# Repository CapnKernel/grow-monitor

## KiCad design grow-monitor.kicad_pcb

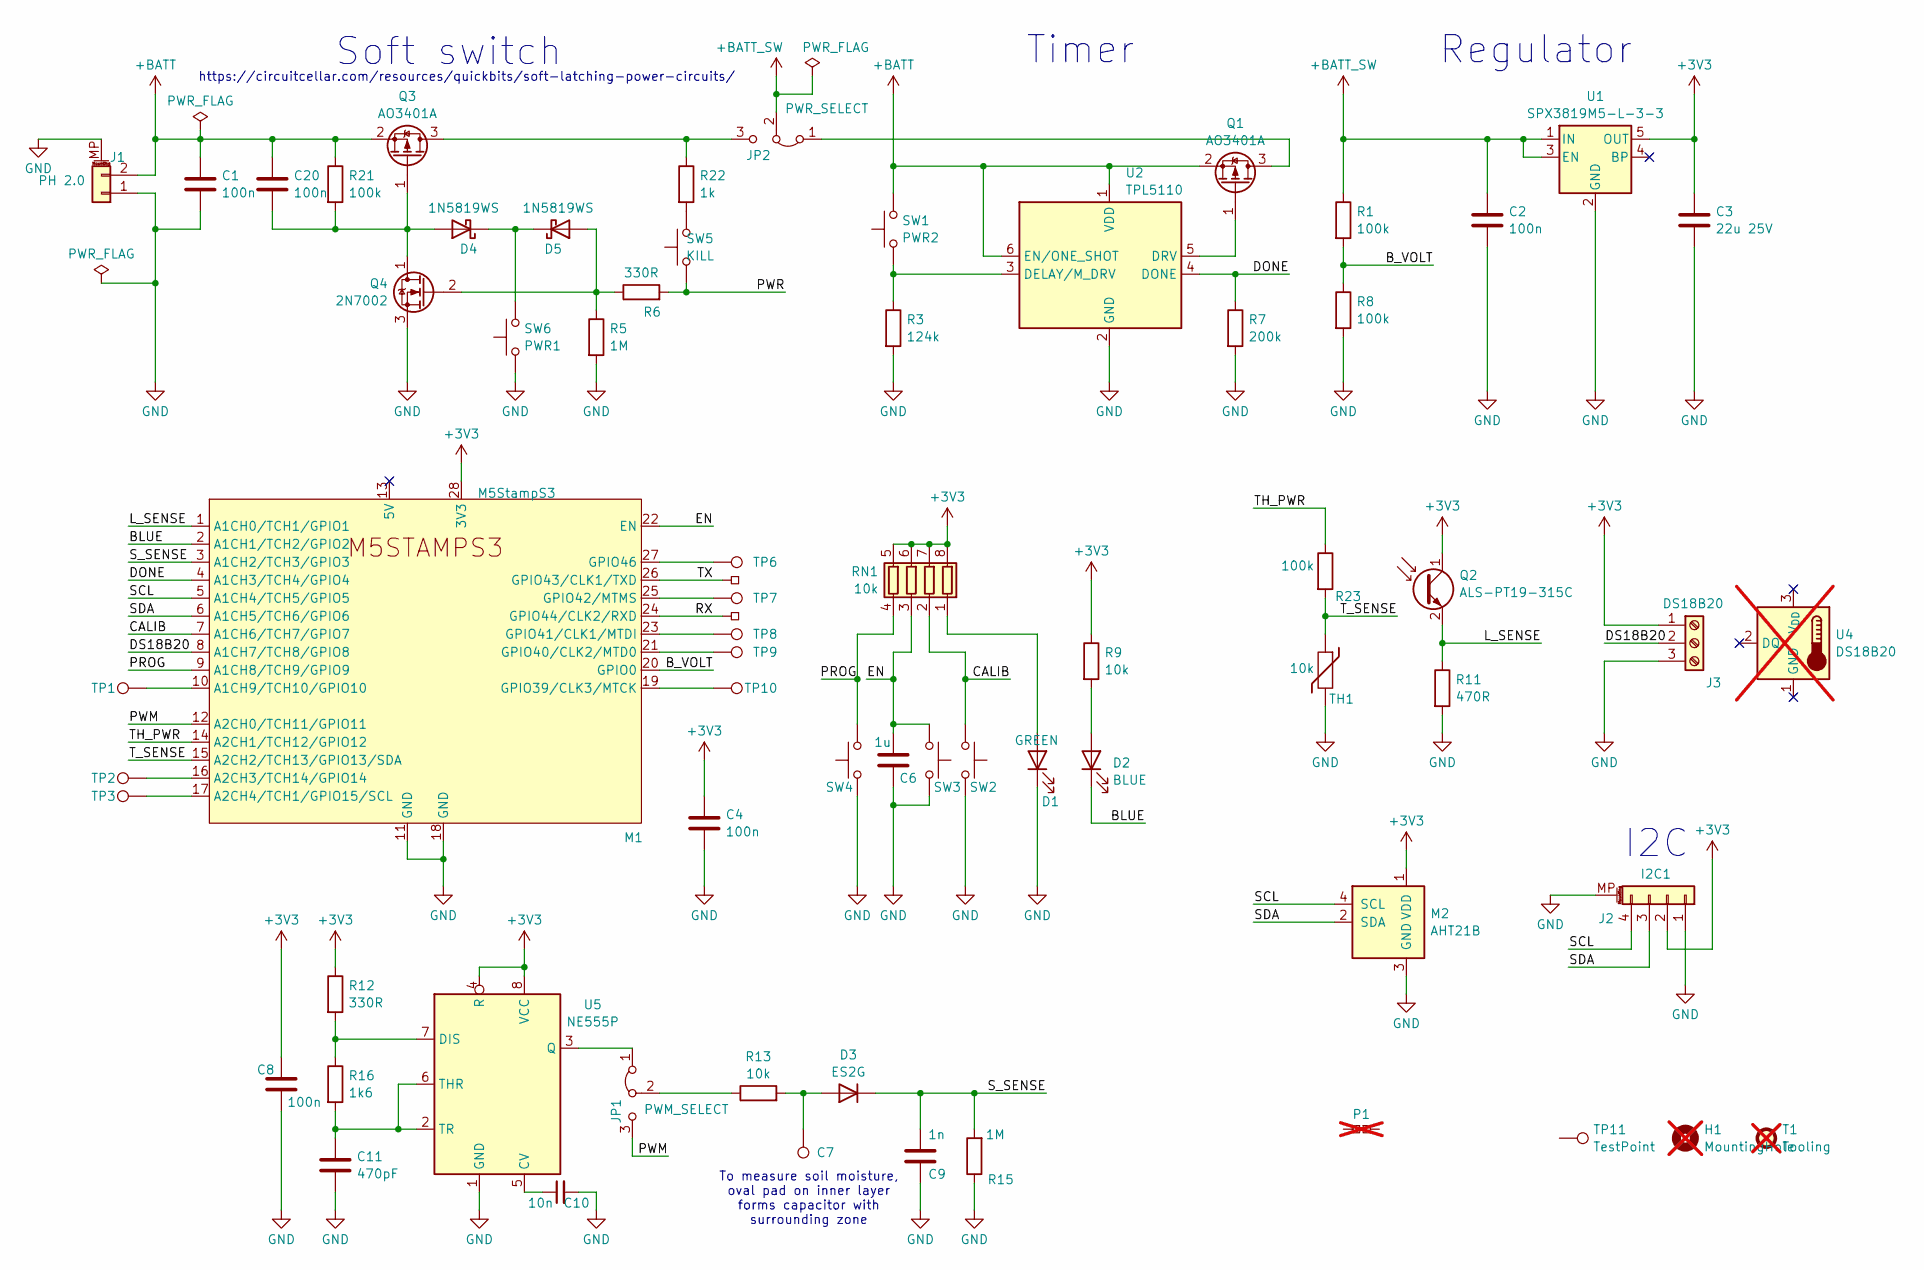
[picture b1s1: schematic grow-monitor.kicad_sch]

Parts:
C1, C2, C4, C8, C20: 100n; C_0603_1608Metric
C3: 22u 25V; C_0805_2012Metric; LCSC C45783
C6: 1u; C_0603_1608Metric
C7: PCB CAP; pcb-cap
C9: 1n; C_0603_1608Metric
C10: 10n; C_0603_1608Metric
C11: 470pF; C_0603_1608Metric
D1: GREEN; LED_0603_1608Metric
D2: BLUE; LED_0603_1608Metric
D3: ES2G; D_SMA; LCSC C2848675
D4, D5: 1N5819WS; D_SOD-323; LCSC C191023
H1: MountingHole; not fitted
J1: PH 2.0; JST_PH_S2B-PH-SM4-TB_1x02-1MP_P2.00mm_Horizontal
J2: I2C1; JST_SH_SM04B-SRSS-TB_1x04-1MP_P1.00mm_Horizontal
J3: DS18B20; PinHeader_1x03_P2.54mm_Vertical
JP1: PWM_SELECT; SolderJumper-3_P1.3mm_Bridged12_Pad1.0x1.5mm
JP2: PWR_SELECT; SolderJumper-3_P1.3mm_Bridged12_Pad1.0x1.5mm
JP5, JP6: PCB_Pin_Breakout; TestPoint_Pad_1.0x1.0mm
M1: M5StampS3; STAMP-S3-DIP
M2: AHT21B; LCSC C3012624
P1: PCB_Patch; SolderJumper-2_P1.3mm_Bridged_Pad1.0x1.5mm; not fitted
Q1, Q3: AO3401A; SOT-23
Q2: ALS-PT19-315C; D_0603_1608Metric; LCSC C146233
Q4: 2N7002; SOT-23
R1, R8, R21, R23: 100k; R_0603_1608Metric
R3: 124k; R_0603_1608Metric
R5, R15: 1M; R_0603_1608Metric
R6, R12: 330R; R_0603_1608Metric
R7: 200k; R_0603_1608Metric
R9, R13: 10k; R_0603_1608Metric
R11: 470R; R_0603_1608Metric
R16: 1k6; R_0603_1608Metric
R22: 1k; R_0603_1608Metric
RN1: 10k; R_Array_Convex_4x0603; LCSC C29718
SW1: PWR2; SW_Push_SPST_NO_432; LCSC C707339
SW2: CALIB; SW_Push_SPST_NO_432; LCSC C707339
SW3: EN; SW_Push_SPST_NO_432; LCSC C707339
SW4: PROG; SW_Push_SPST_NO_432; LCSC C707339
SW5: KILL; SW_Push_SPST_NO_432
SW6: PWR1; SW_Push_SPST_NO_432; LCSC C707339
T1: Tooling; JLC_Tooling_Hole; not fitted
TH1: 10k; R_0805_2012Metric; LCSC C72672
TP1, TP2, TP3, TP6, TP7, TP8, TP9, TP10, TP11: TestPoint; TestPoint_Pad_1.0x1.0mm
U1: SPX3819M5-L-3-3; SOT-23-5
U2: TPL5110; SOT-23-6
U4: DS18B20; TO-92_Inline; not fitted
U5: NE555P; SOIC-8_3.9x4.9mm_P1.27mm

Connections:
+3V3: C3.1, C4.1, C8.1, J2.2, J3.1, M1.28 (3V3), M2.1 (VDD), Q2.1 (C), R9.1, R12.1, RN1.5 (R4.2), RN1.6 (R3.2), RN1.7 (R2.2), RN1.8 (R1.2), U1.5 (OUT), U5.4 (R), U5.8 (VCC)
+BATT: C1.1, C20.1, J1.2, Q1.2 (S), Q3.2 (S), R21.1, SW1.2, U2.1 (VDD), U2.6 (EN/ONE_SHOT)
+BATT_SW: C2.1, JP2.2 (C), R1.1, U1.1 (IN), U1.3 (EN)
/BLUE: D2.1 (K), M1.2 (A1CH1/TCH2/GPIO2)
/B_VOLT: M1.20 (GPIO0), R1.2, R8.1
/CALIB: M1.7 (A1CH6/TCH7/GPIO7), RN1.2 (R2.1), SW2.2
/DONE: M1.4 (A1CH3/TCH4/GPIO4), R7.1, U2.4 (DONE)
/DS18B20: J3.2, M1.8 (A1CH7/TCH8/GPIO8)
/EN: C6.1, M1.22 (EN), RN1.3 (R3.1), SW3.2
/L_SENSE: M1.1 (A1CH0/TCH1/GPIO1), Q2.2 (E), R11.1
/PROG: M1.9 (A1CH8/TCH9/GPIO9), RN1.4 (R4.1), SW4.2
/PWM: JP1.3 (B), M1.12 (A2CH0/TCH11/GPIO11)
/PWR: R6.2, SW5.1
/RX: JP6.1, M1.24 (GPIO44/CLK2/RXD)
/SCL: J2.4, M1.5 (A1CH4/TCH5/GPIO5), M2.4 (SCL)
/SDA: J2.3, M1.6 (A1CH5/TCH6/GPIO6), M2.2 (SDA)
/S_SENSE: C9.1, D3.1 (K), M1.3 (A1CH2/TCH3/GPIO3), R15.2
/TH_PWR: M1.14 (A2CH1/TCH12/GPIO12), R23.1
/TX: JP5.1, M1.26 (GPIO43/CLK1/TXD)
/T_SENSE: M1.15 (A2CH2/TCH13/GPIO13/SDA), R23.2, TH1.1
GND: C1.2, C2.2, C3.2, C4.2, C6.2, C8.2, C9.2, C10.2, C11.2, D1.1 (K), J1.1, J1.MP (MountPin), J2.1, J2.MP (MountPin), J3.3, M1.11 (GND), M1.18 (GND), M2.3 (GND), Q4.3 (S), R3.2, R5.2, R7.2, R8.2, R11.2, R15.1, SW2.1, SW3.1, SW4.1, SW6.1, TH1.2, U1.2 (GND), U2.2 (GND), U5.1 (GND)
unnamed: D1.2 (A), RN1.1 (R1.1)
unnamed: D2.2 (A), R9.2
unnamed: C7.1, D3.2 (A), R13.2
unnamed: C20.2, D4.2 (A), Q3.1 (G), Q4.1 (D), R21.2
unnamed: D4.1 (K), D5.1 (K), SW6.2
unnamed: D5.2 (A), Q4.2 (G), R5.1, R6.1
unnamed: JP1.1 (A), U5.3 (Q)
unnamed: JP1.2 (C), R13.1
unnamed: JP2.1 (A), Q1.3 (D)
unnamed: JP2.3 (B), Q3.3 (D), R22.1
unnamed: M1.10 (A1CH9/TCH10/GPIO10), TP1.1
unnamed: M1.16 (A2CH3/TCH14/GPIO14), TP2.1
unnamed: M1.17 (A2CH4/TCH1/GPIO15/SCL), TP3.1
unnamed: M1.19 (GPIO39/CLK3/MTCK), TP10.1
unnamed: M1.21 (GPIO40/CLK2/MTD0), TP9.1
unnamed: M1.23 (GPIO41/CLK1/MTDI), TP8.1
unnamed: M1.25 (GPIO42/MTMS), TP7.1
unnamed: M1.27 (GPIO46), TP6.1
unnamed: Q1.1 (G), U2.5 (DRV)
unnamed: R22.2, SW5.2
unnamed: R3.1, SW1.1, U2.3 (DELAY/M_DRV)
unnamed: C10.1, U5.5 (CV)
unnamed: R12.2, R16.1, U5.7 (DIS)
unnamed: C11.1, R16.2, U5.2 (TR), U5.6 (THR)

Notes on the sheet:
Regulator
To measure soil moisture, oval pad on inner layer forms capacitor with surrounding zone
I2C
Timer
https://circuitcellar.com/resources/quickbits/soft-latching-power-circuits/
Soft switch

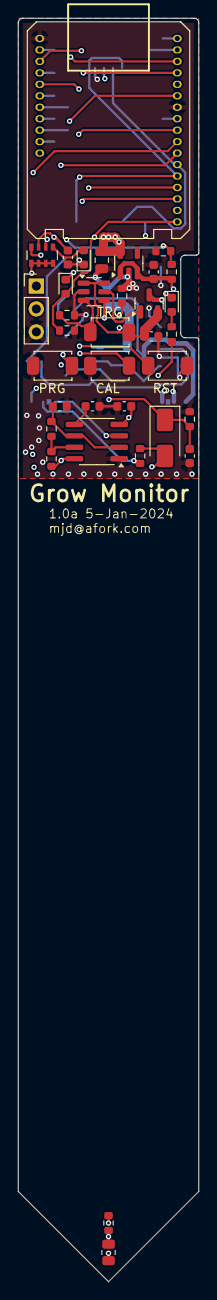
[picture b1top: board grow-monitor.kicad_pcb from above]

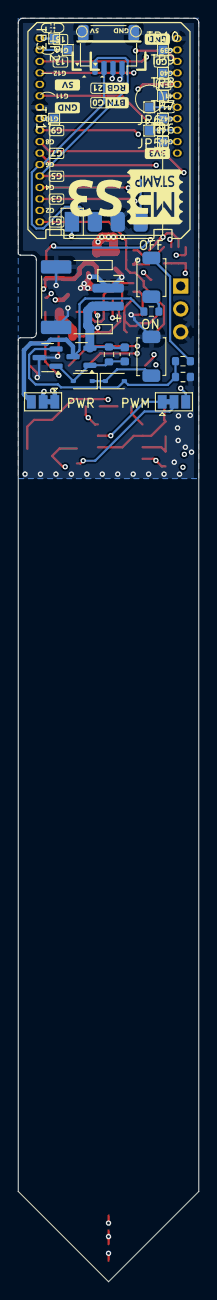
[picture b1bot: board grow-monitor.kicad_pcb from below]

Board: 4 copper layers, 20.0 x 140.0 mm, 62 parts (26 on the bottom side), 45 nets.

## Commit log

2025-01-04 License for this project is CC-BY-SA-NC v4.0
2025-01-04 Empty project files
2025-01-04 First cut
2025-01-04 More improvements
2025-01-05 More tweaks
2025-01-05 Ignore gerbers
2025-01-05 Switched jumpers to use stock cct by default
2025-01-05 Added title, revision, email and date
2025-01-05 Add caps
2025-02-09 Convert to KiCad 9
2025-02-09 Reimport from schematic
2025-05-21 Added schematic
